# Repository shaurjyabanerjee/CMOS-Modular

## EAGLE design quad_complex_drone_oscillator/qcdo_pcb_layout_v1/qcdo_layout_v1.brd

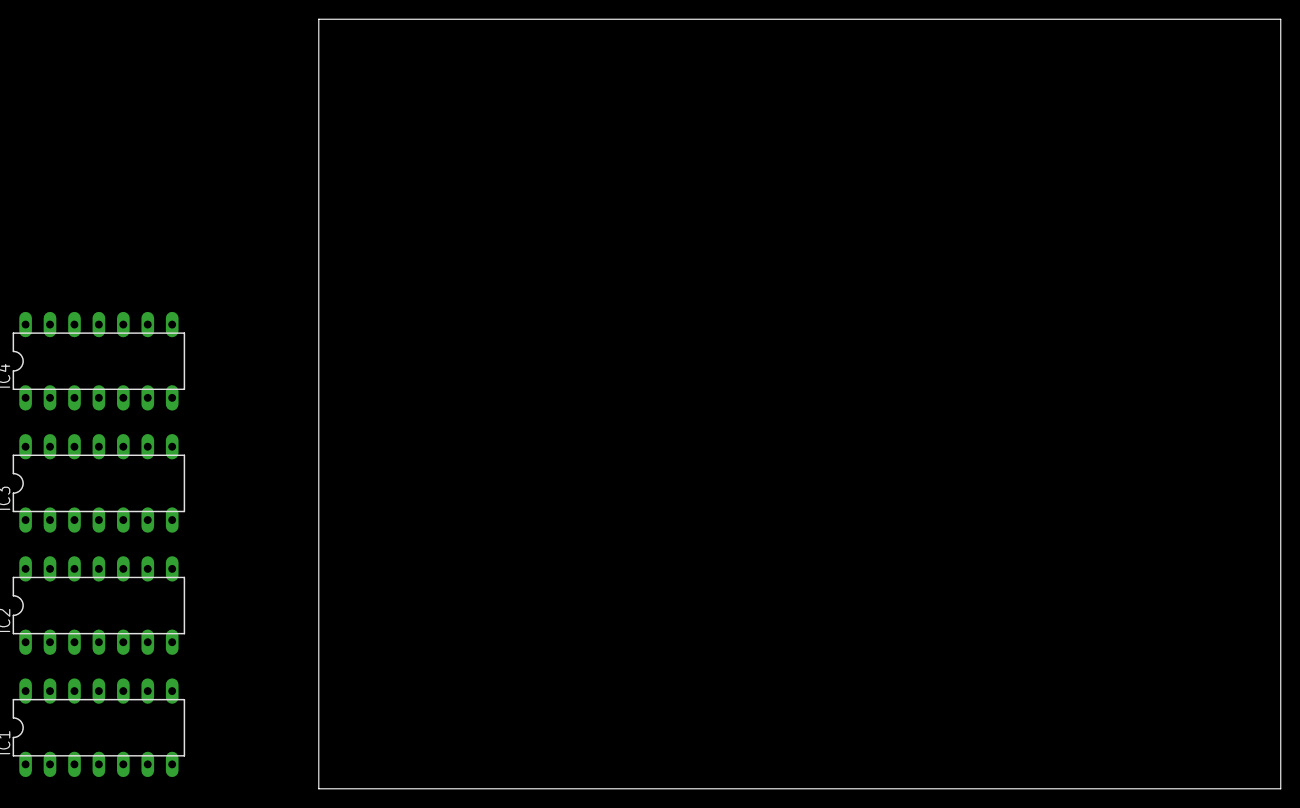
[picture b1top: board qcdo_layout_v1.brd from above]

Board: 2 copper layers, 100.0 x 80.0 mm, 4 parts (0 on the bottom side), 2 nets, no tracks yet.

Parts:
IC1, IC2: 40106N; DIL14
IC3, IC4: 4070N; DIL14

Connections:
VDD: IC1.14, IC2.14, IC3.14, IC4.14
VSS: IC1.7, IC2.7, IC3.7, IC4.7
